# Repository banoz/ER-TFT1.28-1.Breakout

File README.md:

# ER-TFT1.28-1.Breakout
1.28" round TFT display breakout board based on ESP32-S3-BOX schematics.

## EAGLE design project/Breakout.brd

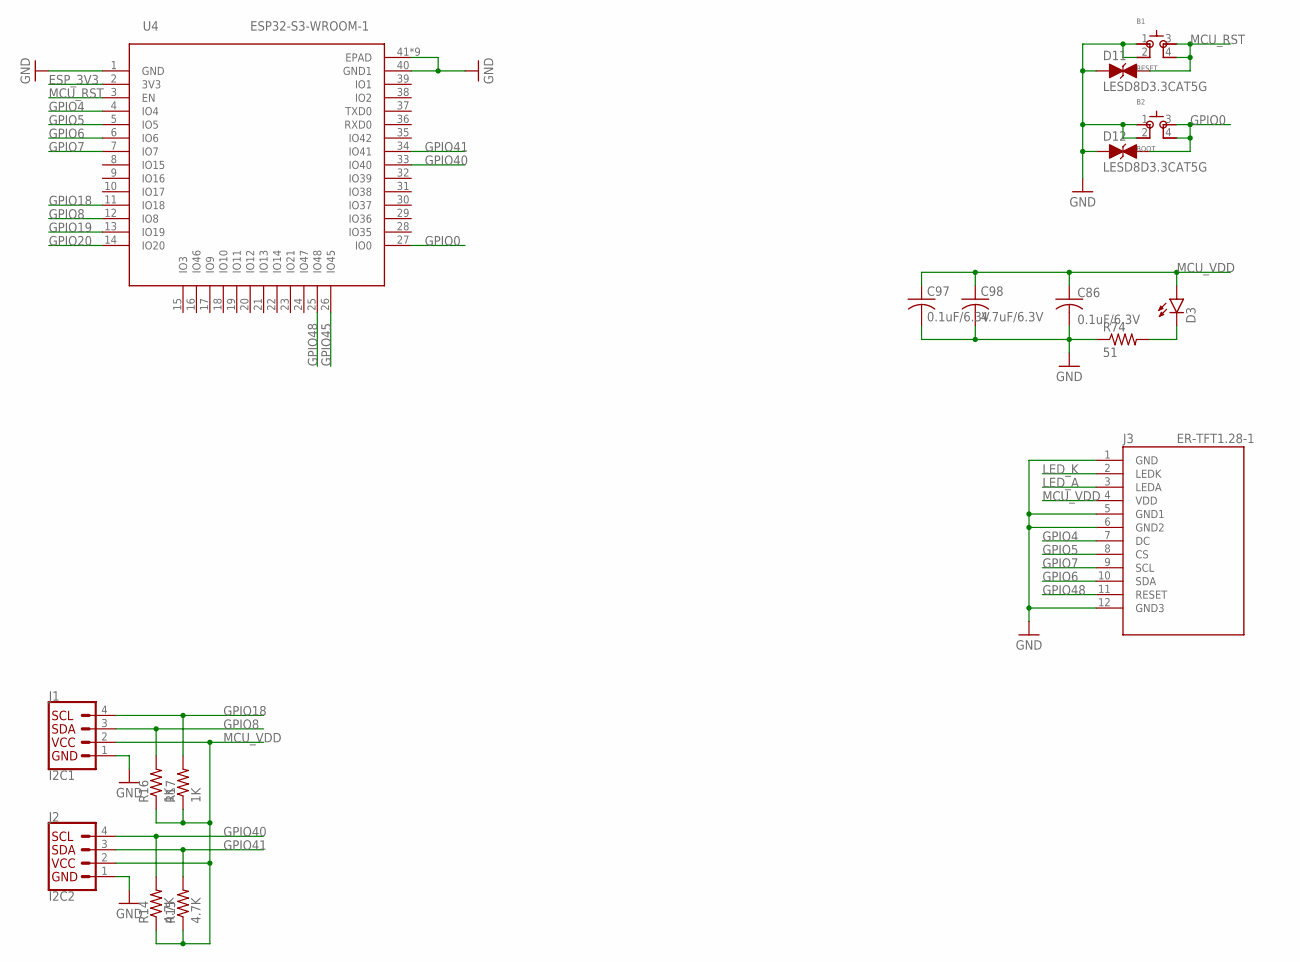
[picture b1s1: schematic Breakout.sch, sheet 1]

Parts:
B1: RESET; SKSCLDE010; LCSC C115362
B2: BOOT; SKSCLDE010; LCSC C115362
C86, C97: 0.1uF/6.3V; C0402; LCSC C541406
C98: 4.7uF/6.3V; C0402; LCSC C106859
D3: LEDCHIPLED_1206; CHIPLED_1206; LCSC C375534
D11, D12: LESD8D3.3CAT5G; SOD882; LCSC C172409
J1: I2C1; JST04_1MM_VERT; LCSC C495539
J2: I2C2; JST04_1MM_VERT; LCSC C495539
J3: ER-TFT1.28-1; 12P-FPC
R14, R15: 4.7K; R0201; LCSC C138135
R16, R17: 1K; R0201; LCSC C138165
R74: 51; R0201; LCSC C163499
U4: ESP32-S3-WROOM-1; QFN60_ESP32-S3-WROOM-1_EXP

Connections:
ESP_3V3: U4.2 (3V3); also elsewhere on the board
GND: B1.1, B1.2, B2.1, B2.2, C86.2, C97.2, C98.2, D11.A, D12.A, J1.1, J2.1, J3.1 (GND), J3.5 (GND1), J3.6 (GND2), J3.12 (GND3), R74.1, U4.1 (GND), U4.40 (GND1), U4.41 (EPAD), U4.42 (EPAD), U4.43 (EPAD), U4.44 (EPAD), U4.45 (EPAD), U4.46 (EPAD), U4.47 (EPAD), U4.48 (EPAD), U4.49 (EPAD); also elsewhere on the board
GPIO0: B2.3 (4), B2.4 (3), D12.C, U4.27 (IO0)
GPIO4: J3.7 (DC), U4.4 (IO4)
GPIO5: J3.8 (CS), U4.5 (IO5)
GPIO6: J3.10 (SDA), U4.6 (IO6)
GPIO7: J3.9 (SCL), U4.7 (IO7)
GPIO8: J1.3, R16.2, U4.12 (IO8)
GPIO18: J1.4, R17.2, U4.11 (IO18)
GPIO19: U4.13 (IO19); also elsewhere on the board
GPIO20: U4.14 (IO20); also elsewhere on the board
GPIO40: J2.4, R14.2, U4.33 (IO40)
GPIO41: J2.3, R15.2, U4.34 (IO41)
GPIO45: U4.26 (IO45); also elsewhere on the board
GPIO48: J3.11 (RESET), U4.25 (IO48); also elsewhere on the board
LED_A: J3.3 (LEDA); also elsewhere on the board
LED_K: J3.2 (LEDK); also elsewhere on the board
MCU_RST: B1.3 (4), B1.4 (3), D11.C, U4.3 (EN); also elsewhere on the board
MCU_VDD: C86.1, C97.1, C98.1, D3.A, J1.2, J2.2, J3.4 (VDD), R14.1, R15.1, R16.1, R17.1; also elsewhere on the board
unnamed: D3.C, R74.2

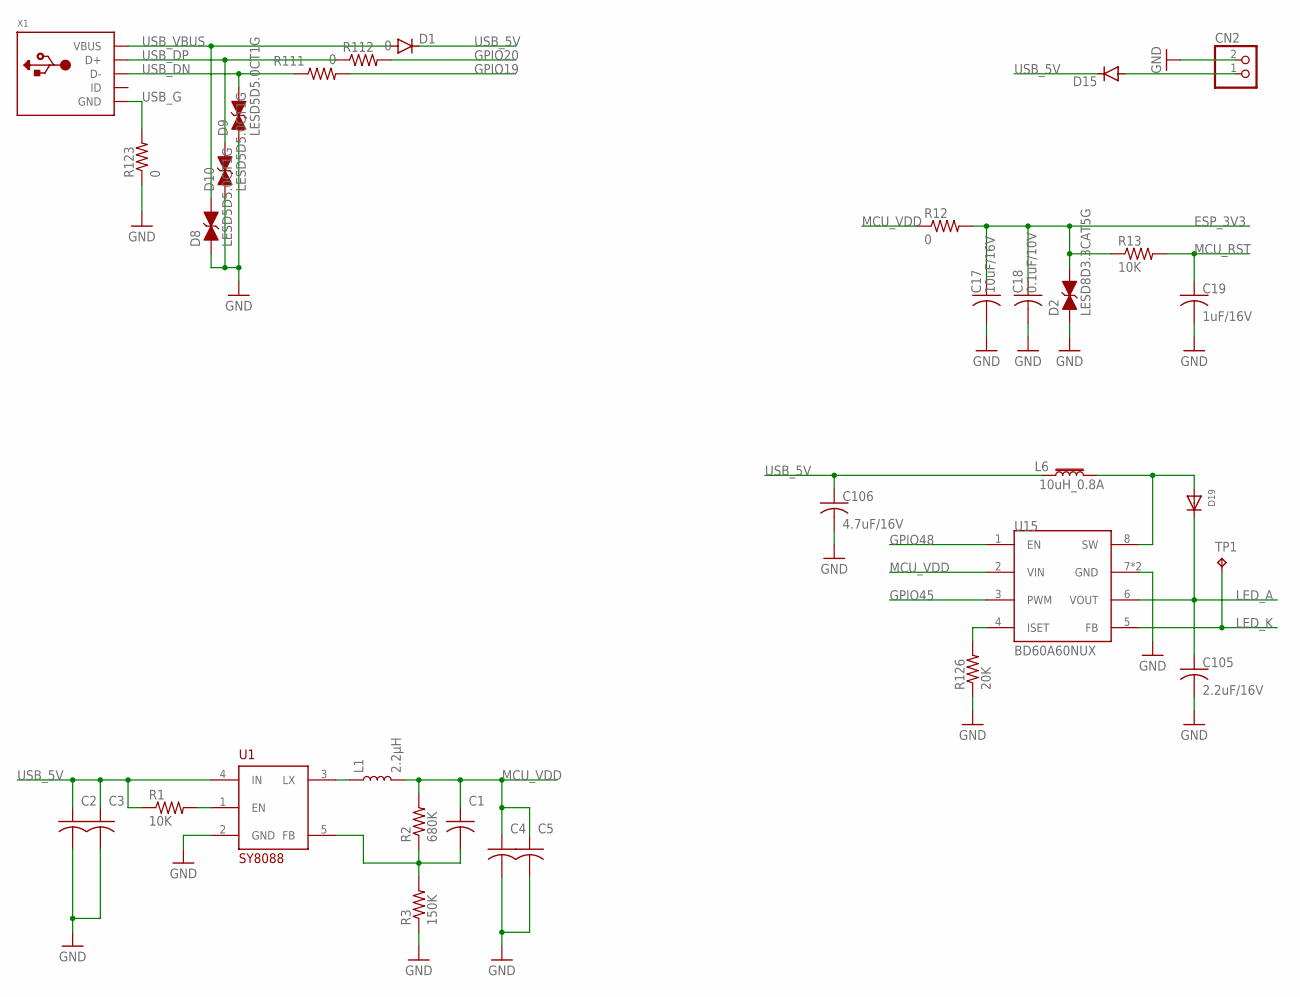
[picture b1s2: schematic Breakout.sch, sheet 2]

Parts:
C1: 22pF/50V; C0402; LCSC C106203
C2, C17: 10uF/16V; C0603; LCSC C86275
C3: 0.1uF/10V; C0603; LCSC C161163
C4, C18: 0.1uF/10V; C0402; LCSC C161163
C5: 10uF/16V; C0402; LCSC C86275
C19: 1uF/16V; C0402; LCSC C77007
C105: 2.2uF/16V; C0603; LCSC C106853
C106: 4.7uF/16V; C0603; LCSC C277476
CN2: JST_2PIN-SMT; JST-PH-2-SMT; LCSC C64658
D1, D15: DIODE-SOD123; SOD123; LCSC C511872
D2: LESD8D3.3CAT5G; SOD882; LCSC C172409
D8, D9, D10: LESD5D5.0CT1G; SOD523; LCSC C383211
D19: DIODESOD-523; SOD-523; LCSC C253516
L1: 2.2μH; INDUCTOR_4X4MM; LCSC C370436
L6: 10uH_0.8A; L3012S; LCSC C518881
R1, R13: 10K; R0402; LCSC C60490
R2: 680K; R0402; LCSC C163456
R3: 150K; R0402; LCSC C93947
R12, R123: 0; R0603; LCSC C100044
R111, R112: 0; R0201; LCSC C106227
R126: 20K; R0402; LCSC C326980
TP1: TPTP06R; TP06R
U1: SY8088; SOT23-5; LCSC C79313
U15: BD60A60NUX; VSON008X2030; LCSC C2678724
X1: MICROBUILDER_USBMICRO_20329; MICROBUILDER_4UCONN_20329; LCSC C40946

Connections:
ESP_3V3: C17.1, C18.1, D2.C, R12.2, R13.1; also elsewhere on the board
GND: C2.2, C3.2, C4.2, C5.2, C17.2, C18.2, C19.2, C105.2, C106.2, CN2.2 (1), D2.A, D8.A, D9.A, D10.A, R3.1, R123.1, R126.1, U1.2 (GND), U15.7 (GND), U15.PAD (GND); also elsewhere on the board
GPIO19: R111.2; also elsewhere on the board
GPIO20: R112.2; also elsewhere on the board
GPIO45: U15.3 (PWM); also elsewhere on the board
GPIO48: U15.1 (EN); also elsewhere on the board
LED_A: C105.1, D19.K (C), U15.6 (VOUT); also elsewhere on the board
LED_K: TP1.TP, U15.5 (FB); also elsewhere on the board
MCU_RST: C19.1, R13.2; also elsewhere on the board
MCU_VDD: C1.1, C4.1, C5.1, L1.P$2 (2), R2.2, R12.1, U15.2 (VIN); also elsewhere on the board
unnamed: D19.A, L6.P$2 (2), U15.8 (SW)
unnamed: CN2.1 (2), D15.A
unnamed: R1.2, U1.1 (EN)
unnamed: L1.P$1 (1), U1.3 (LX)
unnamed: C1.2, R2.1, R3.2, U1.5 (FB)
unnamed: R126.2, U15.4 (ISET)
USB_5V: C2.1, C3.1, C106.1, D1.C, D15.C, L6.P$1 (1), R1.1, U1.4 (IN)
USB_DN: D9.C, R111.1, X1.D-
USB_DP: D10.C, R112.1, X1.D+
USB_G: R123.2, X1.BASE@1 (GND), X1.BASE@2 (GND), X1.GND, X1.SPRT@1 (GND), X1.SPRT@2 (GND), X1.SPRT@3 (GND), X1.SPRT@4 (GND)
USB_VBUS: D1.A, D8.C, X1.VBUS

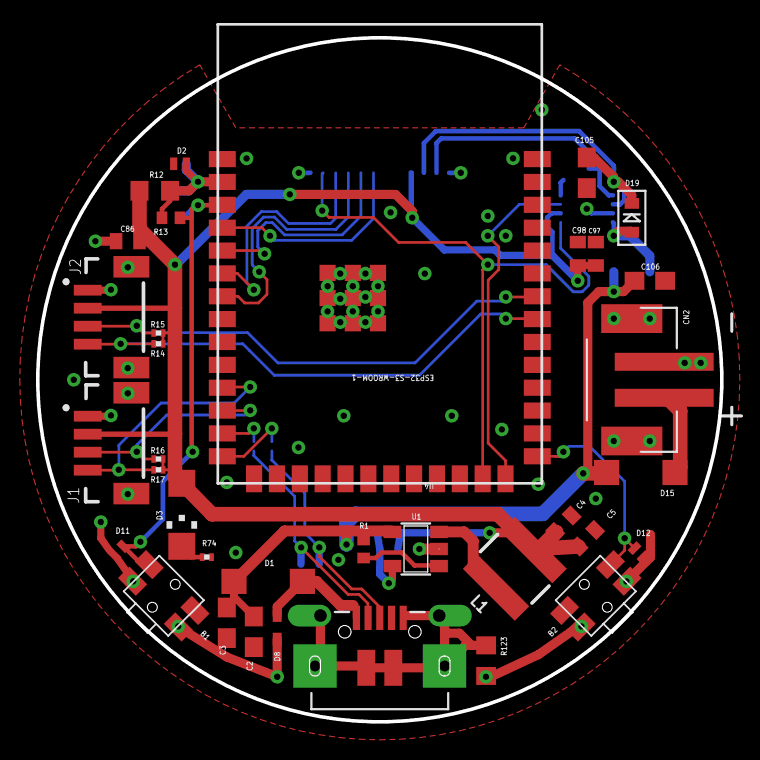
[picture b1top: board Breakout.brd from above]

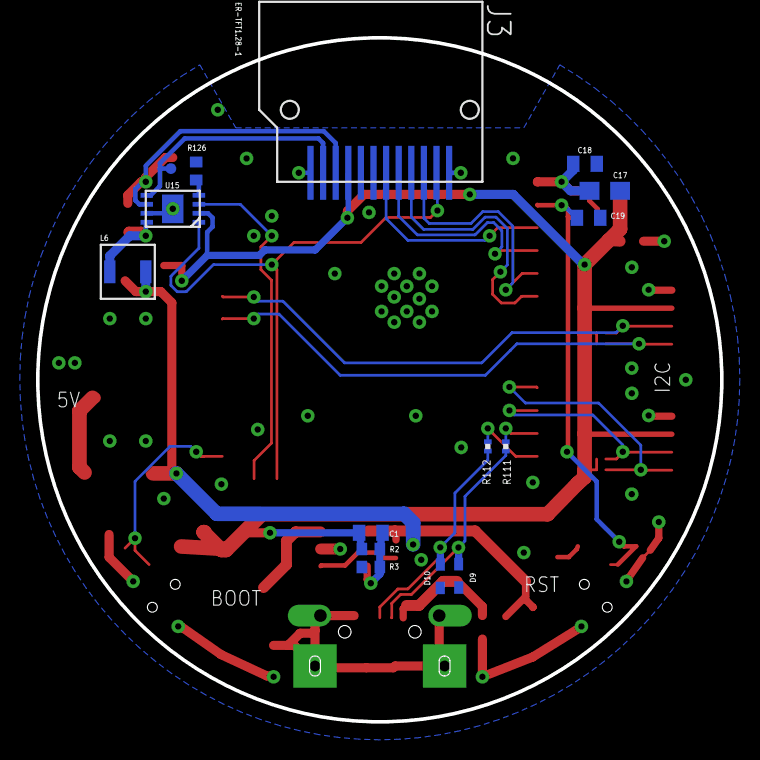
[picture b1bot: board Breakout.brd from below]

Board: 2 copper layers, 38.0 x 38.0 mm, 50 parts (15 on the bottom side), 31 nets.

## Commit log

2021-11-28 Create LICENSE
2021-11-28 Initial state
2021-12-09 Layout complete
2022-05-07 cleanup and fixes
2022-06-18 Display pinout fix

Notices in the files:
parts and their libraries:
SparkFun-Connectors: Licensing: Creative Commons ShareAlike 4.0 International - https://creativecommons.org/licenses/by-sa/4.0
